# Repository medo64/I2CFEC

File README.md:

I²C Framework Expansion Card
============================

Non-isolated I²C master.

## Pinout

To connect to this board, one has to use a 4-pin JST XH connector. The following
table represents the pinout, pin 1 being on the left as looking into the
expansion card.

| # | Ref   | Description                     |
|--:|:-----:|---------------------------------|
| 1 | GND   | Ground connection               |
| 2 | V+    | Positive voltage                |
| 3 | SDA   | Data                            |
| 4 | SCL   | Clock                           |

Output voltage is either 3.3V or 5V at up to 100 mA. Pull-up is done to the same
level.

## LEDs

Left LED signals if serial data is received or sent.

Right LED signals if output is active and there is no fault.

---
*You can check my blog and other projects at [www.medo64.com](https://www.medo64.com/electronics/).*

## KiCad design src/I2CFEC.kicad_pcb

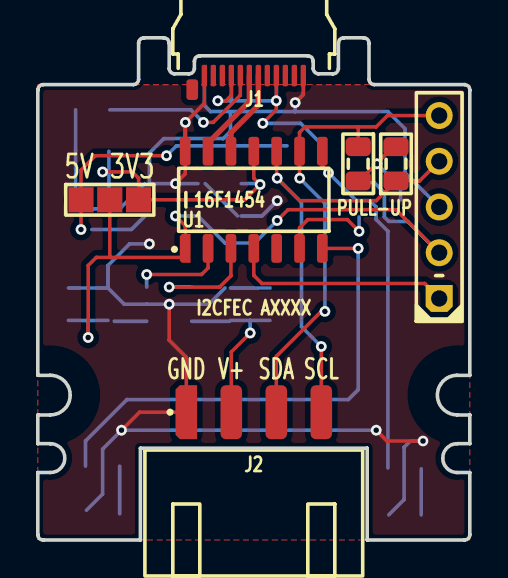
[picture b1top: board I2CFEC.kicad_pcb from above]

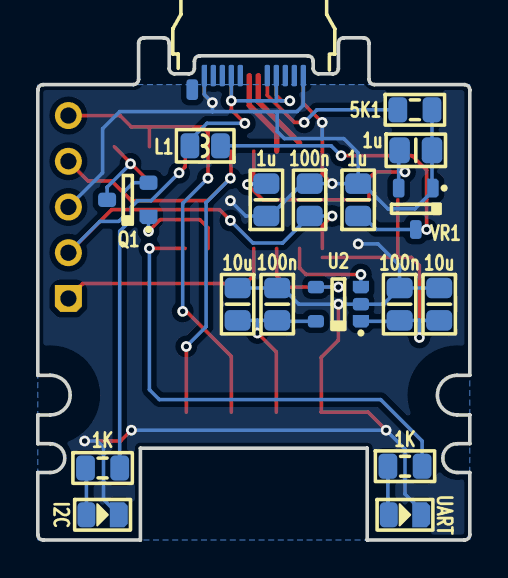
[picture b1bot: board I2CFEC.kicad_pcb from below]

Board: 2 copper layers, 24.0 x 27.9 mm, 24 parts (17 on the bottom side), 20 nets.

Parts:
C1, C2, C3: 100n; C (0805)
C4, C5, C6: 1u; C (0805)
C7, C8: 10u; C (0805)
DS1: UART; DS (0805)
DS2: I2C; DS (0805)
ICSP: Microchip PIC; ICSP PIC Pogo (5w)
J1: 105444-0001; J USB C 3.2 Edge (24w)
J2: B4B-XH-A; J JST XH Edge [I2C] (4w)
JP1: Jumper; JP Dual (1205)
L1: 120R; L (0805)
Q1: BSS84; Q MOSFET-P (SOT23-3)
R1, R2: 1K; R (0805)
R3, R4: 2K2; R (0805)
R5: 5K1; R (0805)
U1: 16F1454; U Micro [PIC16F1454] (SOIC-14)
U2: MIC2091; U LoadSwitch 100mA [MIC2091-1] (SOT23-5)
VR1: MCP1700; VR Linear 3.3V 250mA [MCP1700] (SOT-23)

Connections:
3V3: C4.1, C6.2, JP1.3, U1.11, VR1.2
5V: C5.2, JP1.1, L1.2, VR1.3
A_CC: J1.A5, R5.2
GND: C1.2, C2.2, C3.2, C4.2, C5.1, C6.1, C7.2, C8.2, DS1.1, DS2.1, ICSP.3, J1.A1, J1.A12, J1.B01, J1.B12, J2.1, R5.1, U1.14, U2.2, VR1.1
ICSP_VPP: ICSP.1, U1.4
LED_A: R1.1, U1.7
LED_A': DS1.2, R1.2
LED_B: R2.1, U1.8
LED_B': DS2.2, R2.2
OUT_PULLUP: Q1.1, U1.6
POWER_EN: U1.2, U2.3
POWER_FAULT: U1.3, U2.4
SCL: ICSP.4, J2.4, R3.1, U1.10
SDA: ICSP.5, J2.3, R4.1, U1.9
USB_DM: J1.A7, U1.12
USB_DP: J1.A6, U1.13
VDD: C1.1, C2.1, C7.1, ICSP.2, JP1.2, Q1.2, U1.1, U2.1
VDD_OUT: C3.1, C8.1, J2.2, U2.5
VDD_PULLUP: Q1.3, R3.2, R4.2
Vin: J1.A4, J1.A9, J1.B04, J1.B09, L1.1

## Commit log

2024-09-01 Updated footprints
2024-09-02 Moved directory
2024-09-02 Added pullup mosfet
2024-09-02 Updating part names
2024-10-03 Adjusted 3.3/5V selection
2024-10-03 Moving components around - a lot
2024-10-03 Refactoring some more
